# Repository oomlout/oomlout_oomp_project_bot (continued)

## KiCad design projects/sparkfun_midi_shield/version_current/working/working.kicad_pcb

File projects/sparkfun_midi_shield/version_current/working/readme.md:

# OOMP Project  
## MIDI_Shield  by sparkfun  
  
oomp key: oomp_projects_flat_sparkfun_midi_shield  
(snippet of original readme)  
  
SparkFun MIDI Shield  
====================  

[*SparkFun MIDI Shield (DEV-12898)*](https://www.sparkfun.com/products/12898)  
  
The MIDI Shield gives your Arduino access to the MIDI communication protocol, so you can control synthesizers, sequencers, and other musical devices.  
  
Repository Contents  
-------------------  
  
* **/Firmware** - Example Arduino .ino sketch  
* **/Hardware** - All Eagle design files (.brd, .sch)  
* **/Production** - Production panel files (.brd)  
  
Documentation  
--------------  
* **[Hookup Guide](https://learn.sparkfun.com/tutorials/midi-shield-hookup-guide?_ga=1.24780723.863167751.1453149924)** - Basic hookup guide for the MIDI Shield.  
* **[SparkFun Fritzing repo](https://github.com/sparkfun/Fritzing_Parts)** - Fritzing diagrams for SparkFun products.  
* **[SparkFun 3D Model repo](https://github.com/sparkfun/3D_Models)** - 3D models of SparkFun products.   
* **[SparkFun Graphical Datasheets](https://github.com/sparkfun/Graphical_Datasheets)** -Graphical Datasheets for various SparkFun products.  
  
Product Versions  
----------------  
* [DEV-12898](https://www.sparkfun.com/products/12898)- Version 1.5. R3 compatible. Currently live.   
* [DEV-09595](https://www.sparkfun.com/products/retired/9595)- Version 1.3. Retired.   
  
Version History  
---------------  
* [V_1.5](https://github.com/sparkfun/MIDI_Shield/tree/V_1.5) - GitHub snapshot at V_1.5.   
* [V_  
  full source readme at [readme_src.md](readme_src.md)  
  
source repo at: [https://github.com/sparkfun/MIDI_Shield](https://github.com/sparkfun/MIDI_Shield)  
## Board  

## Schematic  

[schematic pdf](working_schematic.pdf)  
## Images

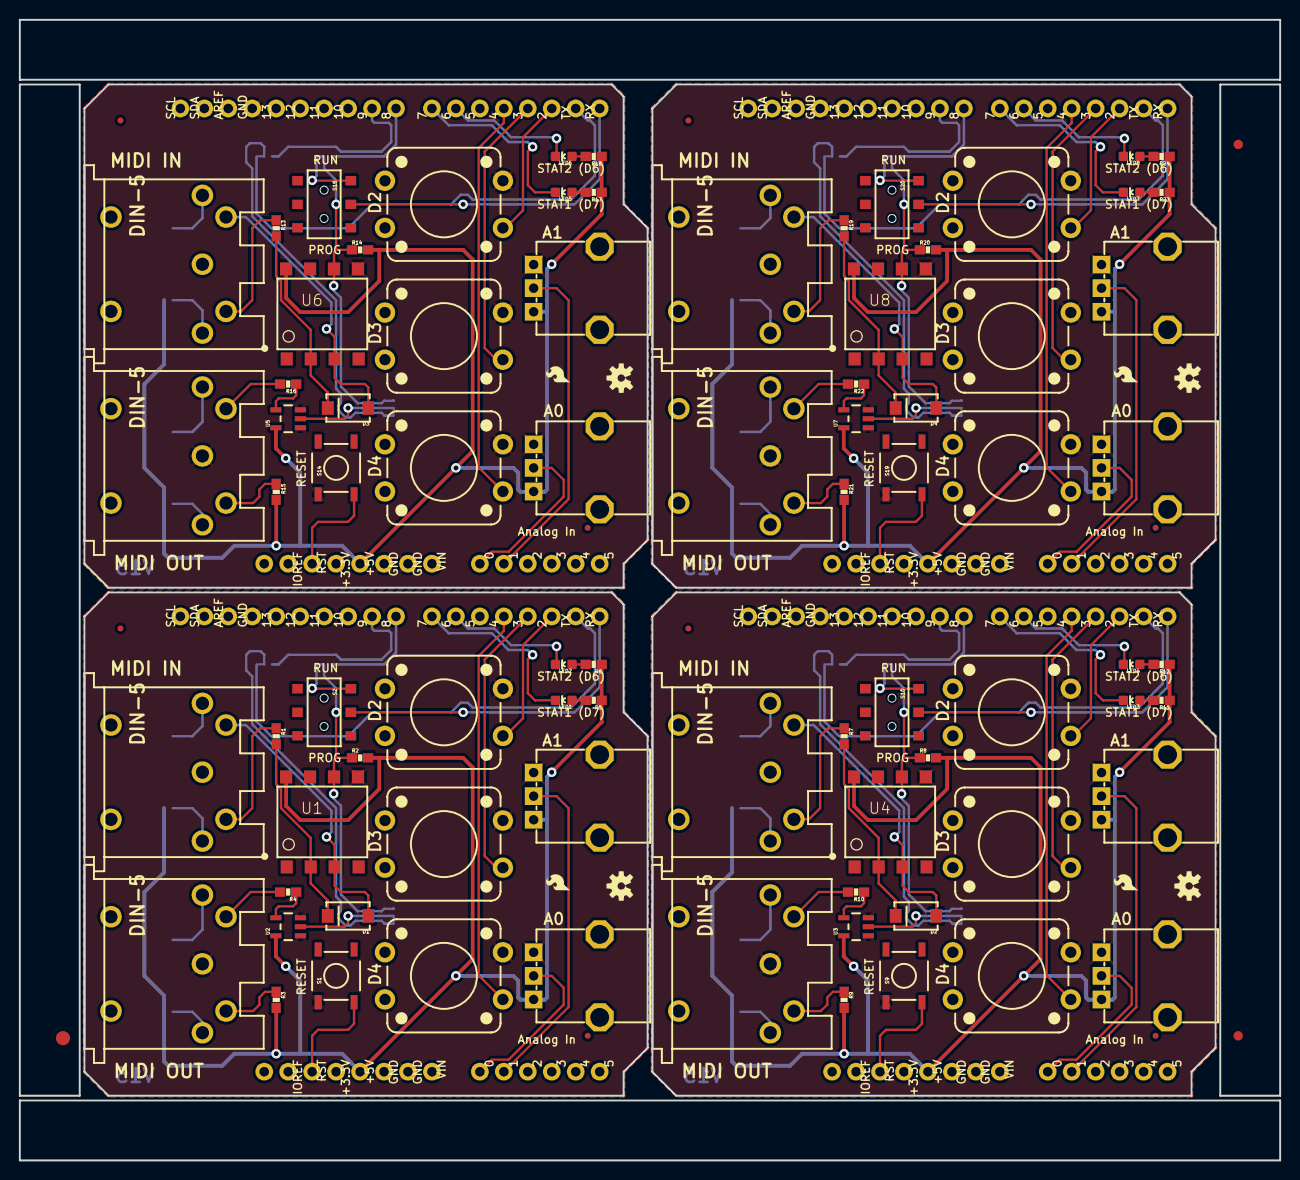
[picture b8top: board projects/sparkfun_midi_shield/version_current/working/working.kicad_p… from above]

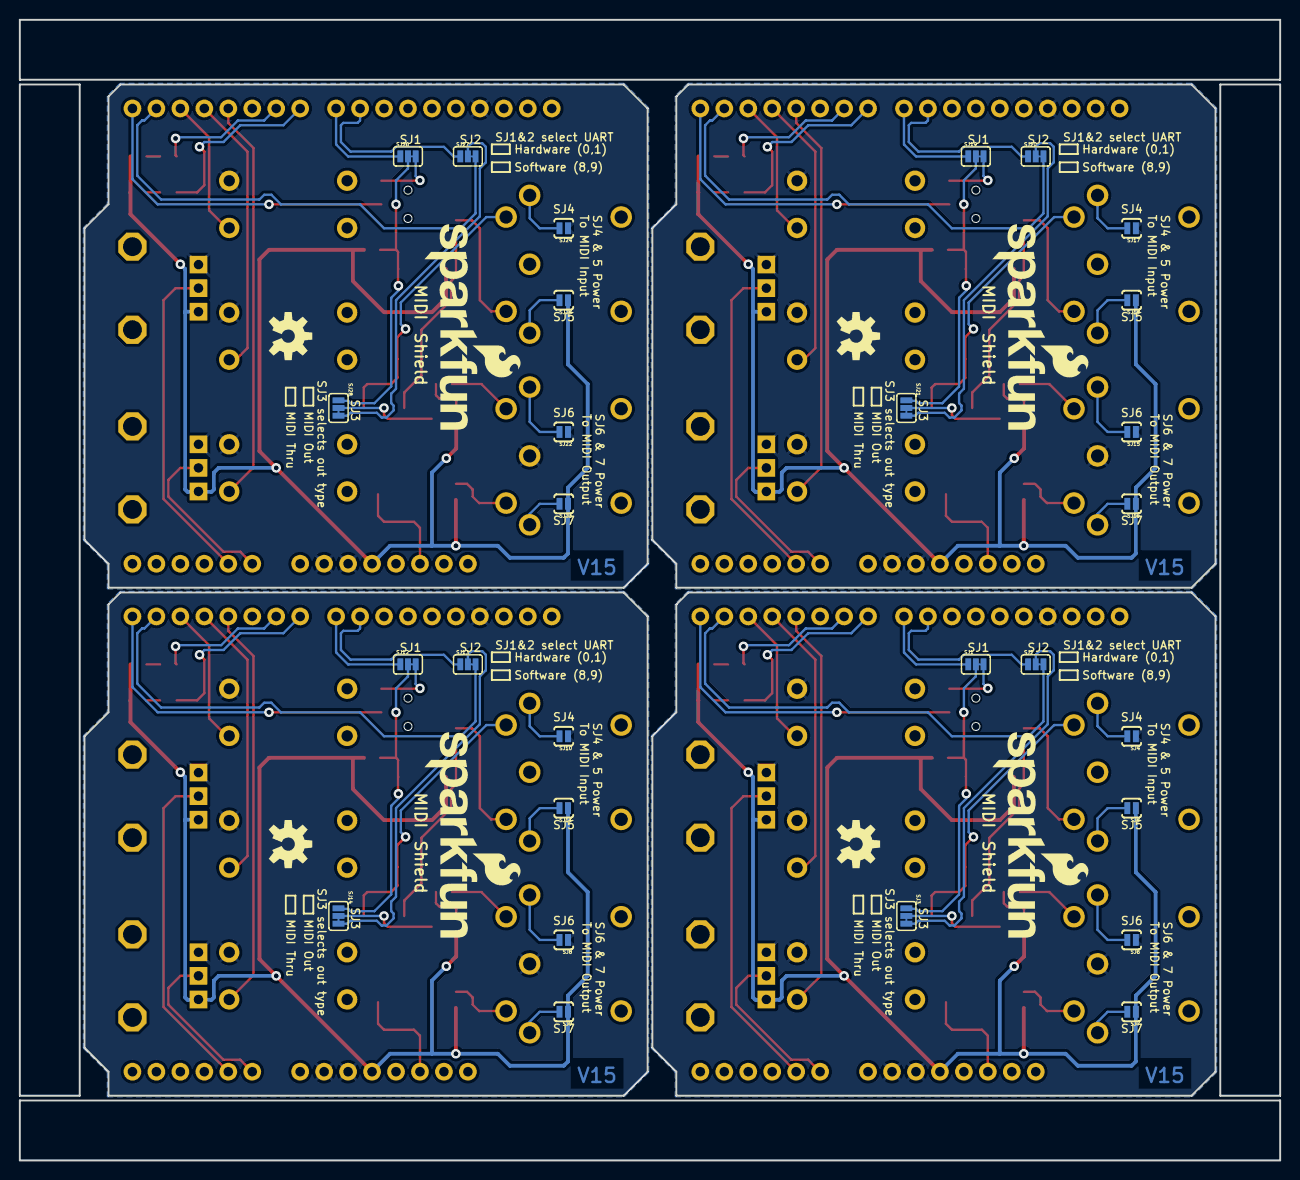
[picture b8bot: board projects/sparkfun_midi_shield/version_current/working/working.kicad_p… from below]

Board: 2 copper layers, 133.6 x 120.9 mm, 139 parts (36 on the bottom side), 120 nets.

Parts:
D1, D2, D3, D4: MBRA140; SMA-DIODE
E$1: FIDUCIAL-1.5X3
E$4, E$5: FIDUCIAL-1X2
FID1, FID2, FID3, FID4, FID5, FID6, FID7, FID8: FIDUCIALUFIDUCIAL; MICRO-FIDUCIAL
J1, J4, J7, J10: MIDI IN; 5-PIN-DIN-RA-PCB-NEW
J2, J5, J8, J11: MIDI OUT; 5-PIN-DIN-RA-PCB-NEW
J3, J6, J9, J12: UNO_R3_SHIELD
LED1, LED3, LED5, LED7: RED; LED-0603
LED2, LED4, LED6, LED8: GREEN; LED-0603
LOGO1, LOGO4, LOGO9, LOGO13: SFE_LOGO_NAME_FLAME.2_INCH; SFE_LOGO_NAME_FLAME_.2
LOGO2, LOGO6, LOGO10, LOGO14: OSHW-LOGOS; OSHW-LOGO-S
LOGO3, LOGO7, LOGO11, LOGO15: OSHW-LOGOM; OSHW-LOGO-M
LOGO5, LOGO8, LOGO12, LOGO16: SFE_LOGO_FLAME.1_INCH; SFE_LOGO_FLAME_.1
R1, R2, R3, R4, R7, R8, R9, R10, R13, R14, R15, R16, R19, R20, R21, R22: 220; 0603-RES
R5, R6, R11, R12, R17, R18, R23, R24: 330; 0603-RES
RV1, RV2, RV3, RV4, RV5, RV6, RV7, RV8: 10k; ALPS_POT
S1, S9, S14, S19: Reset; TACTILE-SWITCH-SMD
S2, S10, S15, S20: RUN/PROGRAM; AYZ0202
S3, S4, S5, S6, S7, S8, S11, S12, S13, S16, S17, S18: SWITCH-MOMENTARY-212MM; TACTILE-PTH-12MM
SJ1, SJ12, SJ19, SJ26: RX sel; PAD-JUMPER-3-2OF3_NC_BY_TRACE_YES_SILK_FULL_BOX
SJ2, SJ13, SJ20, SJ27: TX sel; PAD-JUMPER-3-2OF3_NC_BY_TRACE_YES_SILK_FULL_BOX
SJ3, SJ14, SJ21, SJ28: out/thru; PAD-JUMPER-3-2OF3_NC_BY_TRACE_YES_SILK_FULL_BOX
SJ4, SJ5, SJ6, SJ7, SJ8, SJ9, SJ10, SJ11, SJ15, SJ16, SJ17, SJ18, SJ22, SJ23, SJ24, SJ25: JUMPER-PAD-2-NOYES_SILK; PAD-JUMPER-2-NO_YES_SILK
U1, U4, U6, U8: 6N138M; 8-SMD
U2, U3, U5, U7: 74AHC1G125; SOT23-5

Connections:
1: D2.C, R7.2, U4.2
2: J5.4, R9.1
3: D3.C, R13.2, U6.2
4: J8.4, R15.1
5: D4.C, R19.2, U8.2
6: J11.4, R21.1
56: D1.C, R1.2, U1.2
1235: J2.4, R3.1
A0: J3.A0, RV2.P$2
A1: J3.A1, RV1.P$2
A2: J6.A1, RV3.P$2
A3: J6.A0, RV4.P$2
A4: J9.A1, RV5.P$2
A5: J9.A0, RV6.P$2
A6: J12.A1, RV7.P$2
A7: J12.A0, RV8.P$2
D1: J6.D2, S8.1
D2: J3.D2, S5.1
D3: J3.D3, S4.1
D4: J3.D4, S3.1
D5: J6.D3, S7.1
D6: J3.D6, LED2.C
D7: J3.D7, LED1.C
D8: J6.D4, S6.1
D9: J6.D7, LED3.C
D10: J6.D6, LED4.C
D11: J9.D2, S13.1
D12: J9.D3, S12.1
D13: J9.D4, S11.1
D14: J9.D7, LED5.C
D15: J9.D6, LED6.C
D16: J12.D2, S18.1
D17: J12.D3, S17.1
D18: J12.D4, S16.1
D19: J12.D7, LED7.C
D20: J12.D6, LED8.C
GND: J2.2, J3.GND@0, J3.GND@1, J3.GND@2, RV1.P$1, RV2.P$1, S1.1, S3.3, S4.3, S5.3, SJ4.1, SJ6.1, U1.5, U2.1, U2.3
GND1: J5.2, J6.GND@0, J6.GND@1, J6.GND@2, RV3.P$1, RV4.P$1, S6.3, S7.3, S8.3, S9.1, SJ8.1, SJ10.1, U3.1, U3.3, U4.5
GND2: J8.2, J9.GND@0, J9.GND@1, J9.GND@2, RV5.P$1, RV6.P$1, S11.3, S12.3, S13.3, S14.1, SJ15.1, SJ17.1, U5.1, U5.3, U6.5
GND3: J11.2, J12.GND@0, J12.GND@1, J12.GND@2, RV7.P$1, RV8.P$1, S16.3, S17.3, S18.3, S19.1, SJ22.1, SJ24.1, U7.1, U7.3, U8.5
HARD-RX: S2.1, SJ1.3
HARD-RX1: S10.1, SJ12.3
HARD-RX2: S15.1, SJ19.3
HARD-RX3: S20.1, SJ26.3
HARD-TX: J3.TX, SJ2.3
HARD-TX1: J6.TX, SJ13.3
HARD-TX2: J9.TX, SJ20.3
HARD-TX3: J12.TX, SJ27.3
unnamed: J2.5, R4.2
unnamed: J1.4, R1.1
unnamed: R4.1, U2.4
unnamed: J2.3, SJ6.2
unnamed: J2.1, SJ7.2
unnamed: J1.3, SJ4.2
unnamed: J1.1, SJ5.2
unnamed: LED3.A, R11.2
unnamed: LED1.A, R5.2
unnamed: LED2.A, R6.2
unnamed: LED4.A, R12.2
unnamed: J4.4, R7.1
unnamed: J5.5, R10.2
unnamed: R10.1, U3.4
unnamed: J5.3, SJ8.2
unnamed: J5.1, SJ9.2
unnamed: J4.3, SJ10.2
unnamed: J4.1, SJ11.2
unnamed: LED5.A, R17.2
unnamed: LED6.A, R18.2
unnamed: J7.4, R13.1
unnamed: J8.5, R16.2
unnamed: R16.1, U5.4
unnamed: J8.3, SJ15.2
unnamed: J8.1, SJ16.2
unnamed: J7.3, SJ17.2
unnamed: J7.1, SJ18.2
unnamed: LED7.A, R23.2
unnamed: LED8.A, R24.2
unnamed: J10.4, R19.1
unnamed: J11.5, R22.2
unnamed: R22.1, U7.4
unnamed: J11.3, SJ22.2
unnamed: J11.1, SJ23.2
unnamed: J10.3, SJ24.2
unnamed: J10.1, SJ25.2
PIN1: D2.A, J4.5, U4.3
PIN2: D3.A, J7.5, U6.3
PIN3: D4.A, J10.5, U8.3
PIN5: D1.A, J1.5, U1.3
PORT-RX: R2.1, SJ1.2, SJ3.1, U1.6
PORT-RX1: R8.1, SJ12.2, SJ14.1, U4.6
PORT-RX2: R14.1, SJ19.2, SJ21.1, U6.6
PORT-RX3: R20.1, SJ26.2, SJ28.1, U8.6
PORT-TX: SJ2.2, SJ3.3
PORT-TX1: SJ13.2, SJ14.3
PORT-TX2: SJ20.2, SJ21.3
PORT-TX3: SJ27.2, SJ28.3
RESET: J3.RES, S1.3
RESET1: J6.RES, S9.3
RESET2: J9.RES, S14.3
RESET3: J12.RES, S19.3
RX-I: J3.RX, S2.2
RX-I1: J6.RX, S10.2
RX-I2: J9.RX, S15.2
RX-I3: J12.RX, S20.2
SOFT-RX: J3.D8, SJ1.1
SOFT-RX1: J6.D8, SJ12.1
SOFT-RX2: J9.D8, SJ19.1
SOFT-RX3: J12.D8, SJ26.1
SOFT-TX: J3.D9, SJ2.1
SOFT-TX1: J6.D9, SJ13.1
SOFT-TX2: J9.D9, SJ20.1
SOFT-TX3: J12.D9, SJ27.1
TX-BUF: SJ3.2, U2.2
TX-BUF1: SJ14.2, U3.2
TX-BUF2: SJ21.2, U5.2
TX-BUF3: SJ28.2, U7.2
VCC: J3.5V, R2.2, R3.2, R5.1, R6.1, RV1.P$3, RV2.P$3, SJ5.1, SJ7.1, U1.8, U2.5
VCC1: J6.5V, R8.2, R9.2, R11.1, R12.1, RV3.P$3, RV4.P$3, SJ9.1, SJ11.1, U3.5, U4.8
VCC2: J9.5V, R14.2, R15.2, R17.1, R18.1, RV5.P$3, RV6.P$3, SJ16.1, SJ18.1, U5.5, U6.8
VCC3: J12.5V, R20.2, R21.2, R23.1, R24.1, RV7.P$3, RV8.P$3, SJ23.1, SJ25.1, U7.5, U8.8
